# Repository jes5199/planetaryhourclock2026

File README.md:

# Planetary Hour Clock

A clock that shows the planetary hour, the day of the week, and the old unequal
(temporal) hours of day and night, all on one printed dial that stays correct
all year. Everything that changes with the seasons is handled by *speed*, not
drawing: the hands and LEDs speed up and slow down, so sunrise is always at the
same place on the dial.

- Two mechanical hands: a temporal hour hand and a gold planetary-hour hand
- An 84-LED day ring, plus 18 LEDs on the star and compass points
- A round AMOLED in the centre showing civil time, the hour's ruling planet, and how long
  the current hour is

The design, the dial and the maths are written up in the design doc,
[The planetary hours clock: how it works](https://claude.ai/artifact/MR7kYXaauj6WffYWu9YXEm).

## Status

| Part | State |
| --- | --- |
| Centre screen | Working: clock face, setup by phone or touchscreen, settings saved in flash |
| Hands | Servo board running our firmware; both servos turn freely past one revolution. Next: link it to the screen board over ESP-NOW (plan in [`hands/README.md`](hands/README.md#link-to-the-screen-board-planned-esp-now)). |
| Dial PCB | Generated (KiCad 9), DRC clean; LED-window test coupon ready to order |
| LED board | Generated (KiCad 9, DRC clean): 102 LEDs and the 12 V → 5 V power hub, BOM and placement files for JLCPCB assembly; not ordered |
| Power | One 12 V ≥ 3 A brick into the LED board, which feeds the servo board (12 V) and the screen (5 V) |

## Hardware

| Part | What | Notes |
| --- | --- | --- |
| Centre screen and main controller | [Waveshare ESP32-S3-Touch-AMOLED-1.43](https://www.waveshare.com/esp32-s3-touch-amoled-1.43.htm) | 466×466 round AMOLED, touch, PCF85063 RTC |
| Hand drive | [Waveshare Servo Driver with ESP32](https://www.waveshare.com/Servo-Driver-with-ESP32.htm) (ESP32-D0WD-V3, 4 MB flash, CP2102 USB serial) + 2× Feetech STS3215 serial bus servos, 12 V version | On the desk, running `hands/`. The screen board will send the hand angles to it. |
| Servo power | 12 V DC brick, ≥ 2 A, 5.5 × 2.1 mm centre-positive plug | The board passes its input straight to the servos, so it must match their 12 V rating. USB alone runs the ESP32 but not the servos. |
| Main battery (optional) | 3.7 V single-cell LiPo, MX1.25 2-pin plug, ≥ 500 mAh | Charged by the board at 0.5 A. Check polarity before plugging in. |
| RTC backup | Rechargeable 3 V ML1220 on the SH1.0 2-pin "RTC" header | The header trickle-charges, so never use a CR (non-rechargeable) cell. Without one, the time is lost when power is cut and the clock asks to be set up again. |

## Layout

- `firmware/`: the screen board's firmware (PlatformIO). See [`firmware/README.md`](firmware/README.md).
- `hands/`: the servo board's firmware (PlatformIO). See [`hands/README.md`](hands/README.md).
- `hardware/`: the PCBs, generated as KiCad source. See [`hardware/README.md`](hardware/README.md).
- `tools/`: scripts that generate the firmware's time-zone and city tables, and their source data.

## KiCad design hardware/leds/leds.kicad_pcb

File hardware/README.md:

# Hardware

PCBs for the clock, generated as KiCad 9 source by Python scripts. Edit the scripts, not the
`.kicad_pcb` files: re-running a script rewrites its board.

| Board | Script | What |
| --- | --- | --- |
| `dial/dial.kicad_pcb` | `gen_dial.py` | The 146 mm front dial: all the artwork, the LED windows, the centre hole |
| `coupon/coupon.kicad_pcb` | `gen_coupon.py` | A 78 × 34 mm test coupon of eight LED-window styles |
| `leds/leds.kicad_pcb` | `gen_leds.py` | The LED board behind the dial: 102 addressable LEDs, and the clock's power hub |

The dial follows mockup **N · 84-LED day ring** in the "Planetary Hours Dial" design canvas: its
SVG units are converted at 23/102 mm per unit (the 46 mm screen is r = 102 there), which puts
the rim at r = 73 mm, as in the design doc.

## Inks

A PCB has three: **gold** (bare ENIG copper where the solder mask is opened), **black** (the
mask) and **white** (silkscreen). LED windows are a fourth: **bare fibreglass**, with copper
and mask cleared on both faces, lit from an LED board behind.

| Dial element | Ink |
| --- | --- |
| Rim, ring lines, slice edges, ticks, star | Gold |
| Compass rose | Each point split down its spine: anticlockwise facet gold, clockwise facet white; diagonals under cardinals, the rose over everything else |
| Ruler band, daytime half of each slice | Gold, with the day ruler's symbol knocked out in black |
| Ruler band, night quarters | Black, with the night ruler's symbol in white |
| Day names | White, bent along the arc of their band |
| Planet names, hour numerals | White (numerals crossing the rose's white facets are knocked out in black) |
| Daytime half of the hour ring | Copper under the black mask (a faint sheen) |
| 84 rim LEDs, 7 star points, 7 star corners, 4 compass tips | Fibreglass windows, each with a 0.5 mm non-plated pinhole drilled through its centre |

Gold edges are defined by the mask openings; the copper underneath extends 0.1 mm further so
small registration errors don't show bare edges.

## Fab notes

- **Thickness 0.8 mm** (in the board stackup): brighter windows than 1.6 mm.
- **Black solder mask, white silkscreen, ENIG finish**, both sides (also in the stackup).
- The centre hole (6.5 mm) clears the hands' tube stack, all K&S telescoping brass (0.014"
  wall): a fixed 5/32" post that holds the screen and carries its 5 V and GND wires, the gold
  hand's 3/16" tube on it, and the hour hand's 7/32" tube (5.56 mm) outside that. Nothing else
  can hold the screen up: the hands sweep the whole gap between the dial and the screen.
- Four M2.5 standoff holes (2.7 mm, non-plated) at 14 mm radius on the diagonals, inside the
  46 mm screen's shadow so they never show. The hands sweep between the dial and the screen, so
  standoffs go *behind* the dial (to the LED board and frame), not in front. Their screw heads sit on the dial's face, inside the hands' sweep: the lowest hand must
  run at least 2.5 mm above the dial (an M2.5 pan head is ~2 mm tall; the 0.8 mm dial can't be
  countersunk). Decided 2026-11-18.
- Balancing copper on the back: a 45° cross-hatch (0.4 mm lines 2.26 mm apart, ~31% copper against
  the front's ~25%), under the back's black mask and clear of the windows, holes and edge. The
  dial is held only near its centre, so a balanced board bows less at the rim (`BACK_HATCH`).
- 102 pinholes, 0.5 mm non-plated (the usual fab minimum for NPTH; `PINHOLE_D` in `gen_dial.py`).
- Silk glyphs are grown by 0.035 mm so Cormorant Garamond's hairlines survive silkscreen.
- Order the coupon at 0.8 mm and 1.6 mm, light it from behind, and pick a window style (and a
  board thickness) before ordering the dial.

## LED board

Same outline, centre hole and standoff holes as the dial, sitting a few millimetres behind it.
It takes the LED positions from `gen_dial.led_sites()`, so a window and its LED can't drift
apart. Assembled by JLCPCB on **both sides**; 1.6 mm, black mask, ENIG (gold) finish, so it can
carry the servo board.

**Front** (facing the dial): only the 102 LEDs and a 100 nF capacitor each, so it stays flat.
Copper: a 5 V pour plus the data tracks, and a small GND island under the regulator.

**Back**: the power hub and connectors, a GND pour, and four M2.5 holes (58 × 23 mm) for the
servo board, currently in the lower half until the hand mechanism is designed (`SERVO_CENTRE`).
No pour copper within 3 mm of any mounting hole on either face, and no track or via within
3.3 mm of one (the generator bends tracks around them), so a screw head or standoff scratched
through the mask can't short anything. The dial's standoffs are at 14 mm radius, 2.7 mm clear of
the servo board's top edge.

The DC jack, the protection FET, TVS, bulk capacitor, J2 and the regulator sit together at the
bottom right, in the band between the star points and the rim LEDs. J3 is just above the centre hole,
J4 just past the servo board's left end (seen from the front). No pour copper under the servo
board's ESP32 antenna (both faces), since its radio links it to the screen board.

| Connector | Part | Pins | Goes to |
| --- | --- | --- | --- |
| J1 12V IN | SMD 5.5 × 2.1 mm DC jack, XKB DC-005-5A-2.0-SMT (C319134), rated 2.5 A (JLCPCB's data; the "5A" in the name is a series code) | centre +12 V, sleeve GND, switch GND | A regulated 12 V brick (2–3 A is plenty; a bigger one is fine, the jack limits what's drawn). At 6 o'clock, mouth 0.3 mm in from the board edge (so its corners don't overhang): the cord leaves the bottom of the clock |
| J2 12V SERVO | JST XH 2-pin | 1 +12 V, 2 GND | The servo board's barrel jack: a short (10–15 cm, ≥ 22 AWG) lead with a 5.5 × 2.1 mm plug, centre + on pin 1. Use a right-angle plug: a straight one reaches nearly to this board's edge |
| J3 5V SCREEN | JST XH 2-pin, just above the centre hole | 1 +5 V (≈4.7 V, through the SS14), 2 GND | The screen board's 5 V pin (2×14 header J1 pin 4, GND pin 6), wires straight up the centre post |
| J4 LED DATA | HCTL HC-1.25-3PLT (C2845389), 1.25 mm (MX1.25 / PicoBlade-style) 3-pin, surface mount, vertical, on Molex 53398-0371's land pattern (Molex's own part had 6 in stock) | 1 nc, 2 GND, 3 data | The servo board's RGB-LED header H1 (5 V, GND, LED-OUT): a straight 1:1 cable; its 5 V pin lands on nc. Placed 10 mm (courtyard to board edge) past the servo board's left end (seen from the front), where H1's side-entry cable leaves (`J4_CLEAR`), assuming the servo board mounts with its ports, OLED and jacks facing out and its DC jack towards J2. Buzz the cable out: H1's pin-1 end isn't marked. H1 is a 1.25 mm MX1.25/PicoBlade-style header (Waveshare calls it "XH1.25"; checked 2026-11-18: its plug pulls straight out, no latch, so not JST GH), so a double-ended MX1.25 3-pin cable mates with both |

**Power.** 12 V in → Q1, an AO4407A P-channel MOSFET wired as an "ideal diode" for reverse-polarity
protection (drain to the jack, source to the rail, gate to GND through 100k: 13 mΩ, so ~0.05 W at
2 A where a Schottky would drop 0.5 V and make 1 W; reversed, it stays off; its 25 V gate rating
needs no zener) → a 13 V TVS (SMAJ13A) and 100 µF bulk
capacitor, which damp the ring when a live brick is plugged in (the TVS clamps at 21.5 V at its
  full rated pulse, above the regulator's 19 V limit, but hot-plug ringing into 100 µF is far
  smaller than that pulse) → 12 V
to the servo board, and to a TPS563201 buck (3 × 10 µF in, 4.7 µH, 3 × 22 µF out, 56k/10k: 5.07 V,
up to 3 A) → 5 V for the LEDs and, through an SS14, the screen. EN is tied to VIN (both rated
19 V). The regulator's GND pin and input capacitors drop through vias to a GND island on the
front, right under the chip, so the input current loop is a few millimetres. The power path
(jack → Q1 → J2) runs on copper pours. Pad connections to the pours: thermal relief on the
front (the LEDs and their 0402 capacitors, so both ends of each heat evenly during reflow), solid
for every part on the back (the power parts need the copper for current and heat). U1's GND pin
also has two vias straight down to the front island.

Things the hardware doesn't protect against, so the firmware must:
- **Servo stall current.** Two STS3215s stalling draw ~2.7 A each, more than the jack's 2.5 A,
  and through the jack. Set the servos' torque limit so a jammed hand can't
  pull that. Normal running (hands moving slowly, LEDs mostly dim) is well under 1 A.
- **Brightness.** The XL-2020 LEDs draw up to 5 mA per colour, so all 102 at full white is about
  1.5 A, inside the regulator's 3 A. A firmware cap is still sensible (the screen and heat share
  the budget), and the dial only ever lights a few LEDs brightly. Check the colour order (GRB for
  WS2812B) when the firmware first drives them.
- The SS14 on the screen feed exists because the screen board's 5 V header pin **is its USB
  VBUS**: without it, plugging the screen board into a computer while the clock is powered would
  connect this board's 5 V to the computer's USB port, and a computer alone would try to power
  the LEDs.

**Data chain** (written to `leds/led-chain.csv` with each LED's angle): the servo board's two
on-board LEDs come first, then here: rim LEDs 0–83 clockwise from the start of Sunday's slice
(so chain index = the firmware's `dayRingLed`), then the 7 star points, the 7 star corners and the
4 compass tips, each set clockwise. Jumps between sets go through the back. The input runs from
J4 (through 1k, with a 100k pull-down so LED 0's input doesn't float when the servo board is off)
round the back, crosses to the front in the star ring's one gap (between star
points 6 and 0, which the chain jumps through the back), and comes in to LED 0's DIN.

**Parts not in KiCad's library** live in `footprints/jlc.pretty` (`kicadart.Part` looks there
first):
- The LEDs: XINGLIGHT XL-2020RGBC-WS2812B (C5349955), a WS2812B-protocol LED in the 2020 package,
  because Worldsemi's own WS2812B-2020 (C965555) was out of stock. Footprint drawn from its
  datasheet's recommended pattern and numbered like KiCad's WS2812B-2020 (1 DO, 2 GND, 3 DI,
  4 VDD), which is its datasheet top view turned 180°.
- The DC jack: imported from JLCPCB's part data with easyeda2kicad (in the venv:
  `.venv/bin/easyeda2kicad --footprint --3d --lcsc_id C319134 --output footprints/jlc`),
  converted with `kicad-cli fp upgrade`, pads set from XKB's drawing (rev A1, 2025-07-19). Its
  3D model doesn't show in KiCad's render.

**Placement file.** JLCPCB places its *own* library footprint for each part, and those often
differ from KiCad's: the LEDs and the regulator have pin 1 in the opposite corner (180°), and
connectors are centred where KiCad puts pin 1 at the origin. `jlc_ref.py` downloads JLCPCB's
footprint for every LCSC part (easyeda2kicad, cached in `out/jlc-ref/`), matches its pads to ours,
and records the turn and offset; `cpl.py` (KiCad's Python) writes the CPL from the board with those
corrections. Most need 0° or 180°; the SO-8 FET needs 90°. `jlc_ref.py` has an override table
for parts whose JLCPCB pad numbers don't follow their polarity marks (an earlier SS54 numbered
its cathode end "2"; matching by number would have put it in backwards). A check that places JLCPCB's footprints by the
finished CPL lands every pad on ours (within 0.03 mm for the LEDs, 0.2 mm for the regulator and
diodes, where the two libraries' pads differ in size).

**Reviewed** (2026-11-18) eight times by independent agents against the datasheets: pinouts,
the LED chain, the buck design, JLCPCB rules and stock, the CPL against JLCPCB's footprints, and
the fit with the dial. Their findings are fixed above.

Before ordering:
- Upload `out/leds-jlc/` to JLCPCB's quote page and check every part in the assembly preview.
  The CPL is corrected to JLCPCB's footprints, but the back side relies on the mirrored
  convention (180° − angle) that kicad-jlcpcb-tools and KiBot use; JLCPCB doesn't document it and
  has changed it before. Odd back-side angles (U1 at 330°, Q1 at 258°) make a wrong
  convention obvious in the preview. Check especially: the LEDs (data out at the package's marked
  corner, which is the silk tick), U1's pin-1 dot, Q1's pin-1 dot (at its J2-side, inward corner; pin 4, the gate, is beside its 100k), the SMAJ13A's cathode band towards
  the +12 V side, C111's + at the J2 side, and J2/J3's latches.
- Tell JLCPCB the LEDs are MSL 5 (bake before use) and ask for a reflow peak of 245 °C or less:
  the datasheet recommends 240 ± 5 °C for 6 s (260 °C is the absolute maximum), at most two
  reflows, the second within 8 hours of the first and let them choose the reflow order: the back carries the heavy parts (the 11 mm jack, C111, L1), which shouldn't
  hang upside down through a second pass.
- Check stock (2026-11-18): LEDs C5349955 ~80k (listed by LCSC as "XL-2020RGBC-2812B"; its
  datasheet says XL-2020RGBC-WS2812B), jack C319134 ~4.4k, inductor C408410 ~7k at JLCPCB (LCSC's
  product page is broken; fallback Sunlord SWPA5040S4R7MT, C48496), 1.25 mm header C2845389 ~49k,
  AO4407A C16072 ~9k, JST XH C158012 ~474k, TPS563201 ~4.3k. All extended parts.
- A round board with parts near the edge may need JLCPCB's break-off rails for assembly. The rim
  LEDs' pads are 0.93 mm from the edge all the way round, so ask for tabs placed between parts,
  and none at 6 o'clock, where the DC jack's mouth is 0.3 mm in from the edge.
- The through-hole connector pins poke ~1.5 mm out of the front: the gap to the dial (and any
  baffle) has to clear them. J3 sits on the back just above the centre hole, where the hand tubes'
  gears will be: move it (`J3_R`) if the gear train needs that space.
- Measure the servo board's hole spacing with calipers (58 × 23 mm, from Waveshare's dimension
  drawing).
- KiCad's DRC reports 0 errors and 0 unconnected; the only warnings are `lib_footprint_mismatch`,
  because the generator strips the hidden silkscreen from the library footprints.

## Build

```sh
cd hardware
python3 -m venv .venv && .venv/bin/pip install -r requirements.txt
.venv/bin/python gen_dial.py      # -> dial/dial.kicad_pcb
.venv/bin/python gen_coupon.py    # -> coupon/coupon.kicad_pcb
./render.sh dial/dial.kicad_pcb   # DRC + SVG + 3D render into out/ (uses KiCad 9's kicad-cli)

.venv/bin/python gen_leds.py      # -> leds/leds.kicad_pcb, leds-bom.csv, led-chain.csv
./fill_zones.sh leds/leds.kicad_pcb   # fill the copper pours (KiCad's own filler, via its Python)
./render.sh leds/leds.kicad_pcb
./jlc.sh leds/leds.kicad_pcb      # -> out/leds-jlc/: gerbers.zip, bom.csv, cpl.csv for JLCPCB
                                  #    (CPL corrected to JLCPCB's footprints: jlc_ref.py + cpl.py)
```

Boards with parts (`gen_leds.py`) place KiCad's own library footprints (read from the KiCad app),
set their nets, and write tracks, vias and zone outlines; `kicadart.Part` computes pad positions
the way KiCad does, including mirroring for the back. KiCad fills the zones, since its clearance
and island rules decide connectivity; DRC then confirms every pad is connected.

`template.kicad_pcb` is an empty KiCad 9 board with the stackup; scripts append their
`gr_poly`, `gr_circle` and footprint s-expressions to it (`kicadart.py`).

## Fonts

`fonts/` holds Cormorant Garamond (names and numerals) and Noto Sans Symbols (planet
symbols), both under the SIL Open Font License (texts alongside). Noto Sans Symbols has no ☉,
so the Sun is drawn as a ring and dot.

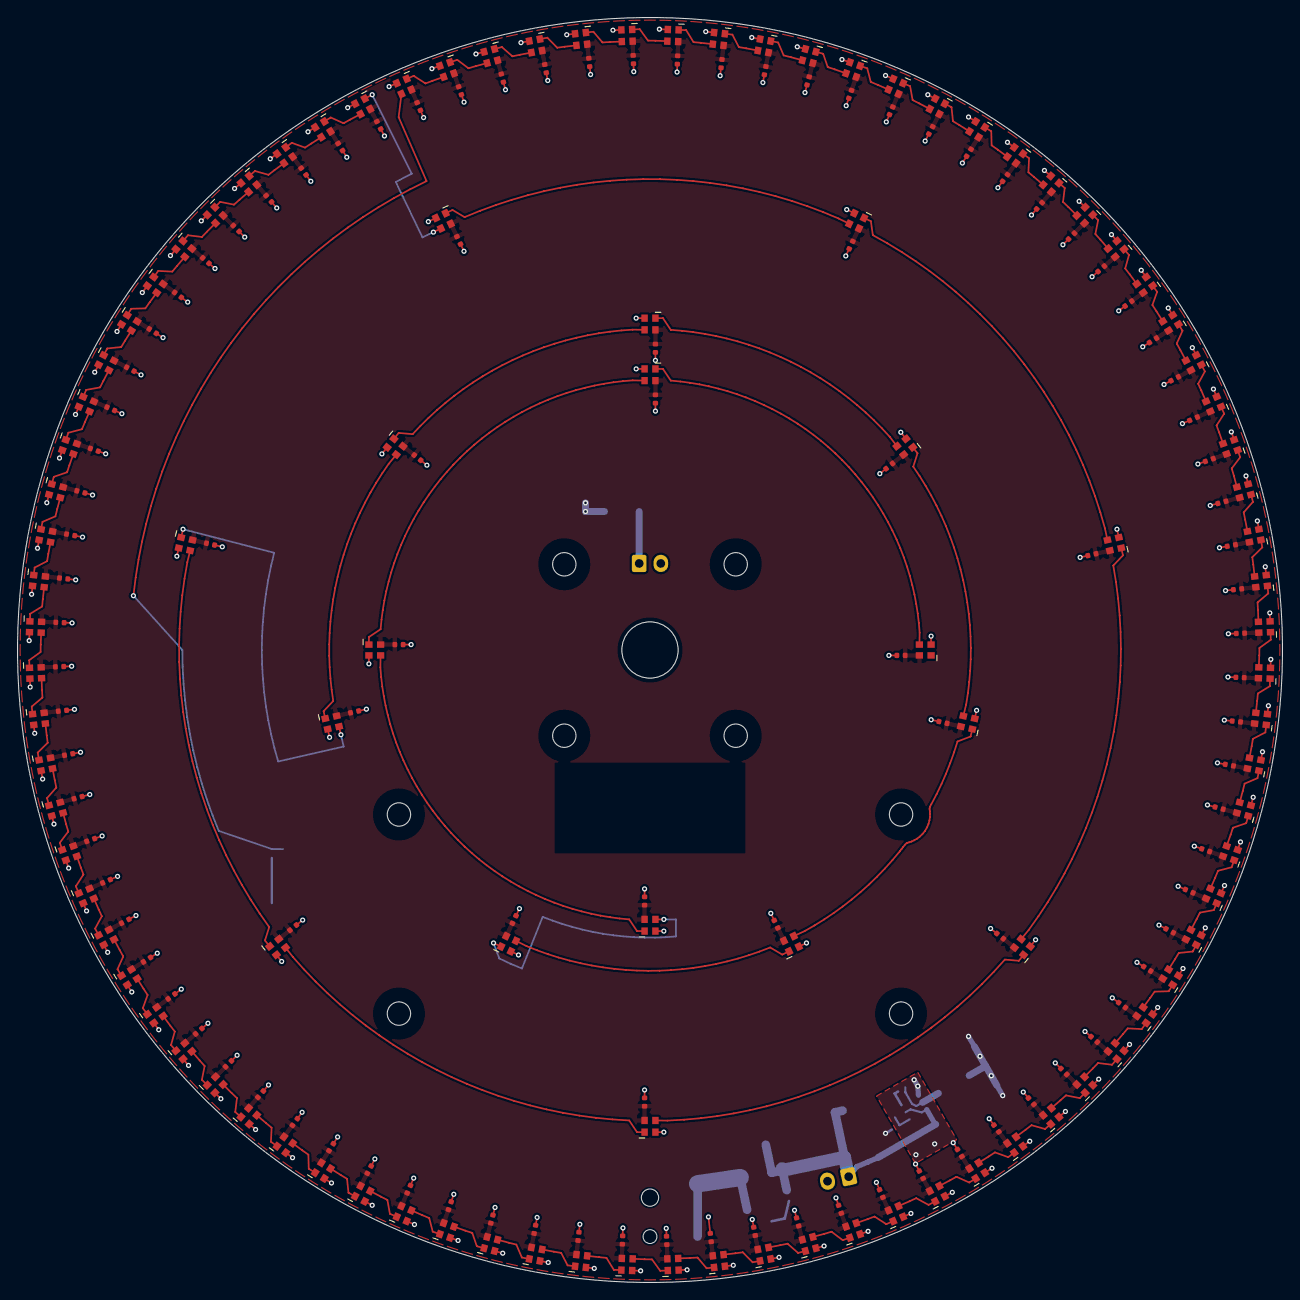
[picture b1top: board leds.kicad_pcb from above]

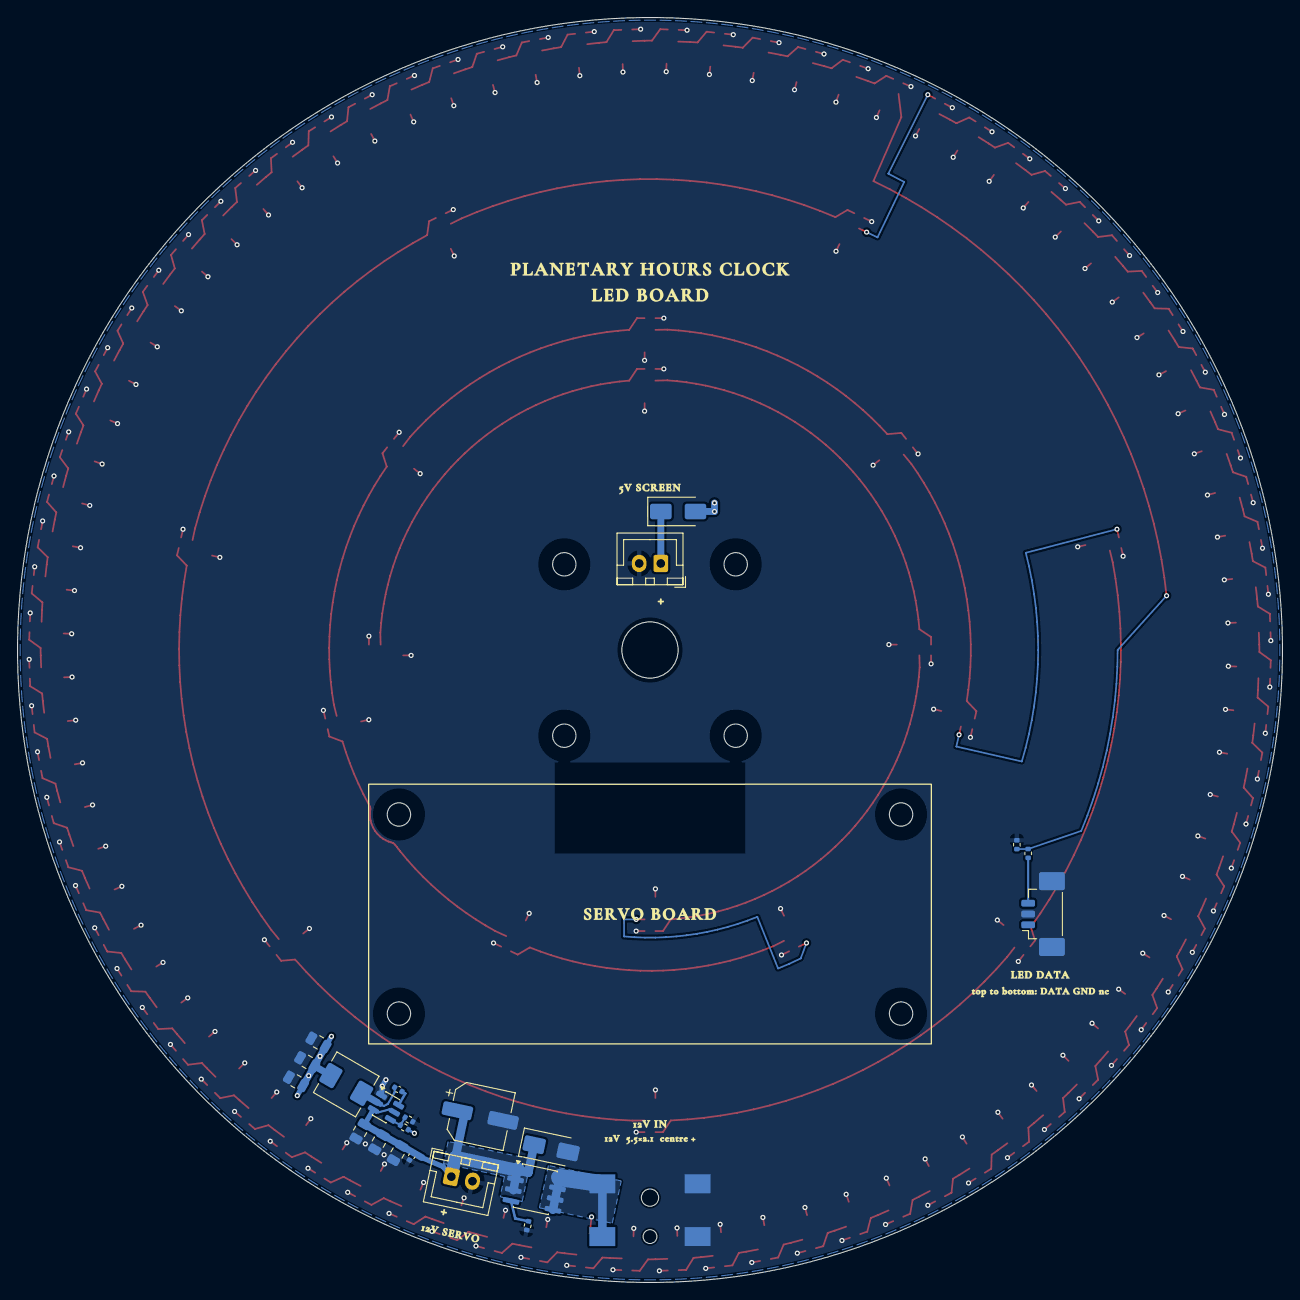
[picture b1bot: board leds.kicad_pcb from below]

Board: 2 copper layers, 146.1 x 146.1 mm, 235 parts (23 on the bottom side), 112 nets.

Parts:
C1, C2, C3, C4, C5, C6, C7, C8, C9, C10, C11, C12, C13, C14, C15, C16, C17, C18, C19, C20, C21, C22, C23, C24, C25, C26, C27, C28, C29, C30, C31, C32, C33, C34, C35, C36, C37, C38, C39, C40, C41, C42, C43, C44, C45, C46, C47, C48, C49, C50, C51, C52, C53, C54, C55, C56, C57, C58, C59, C60, C61, C62, C63, C64, C65, C66, C67, C68, C69, C70, C71, C72, C73, C74, C75, C76, C77, C78, C79, C80, C81, C82, C83, C84, C85, C86, C87, C88, C89, C90, C91, C92, C93, C94, C95, C96, C97, C98, C99, C100, C101, C102, C107: 100nF; C_0402_1005Metric
C103, C104, C105: 10uF 25V; C_0805_2012Metric
C106: 100nF 50V; C_0402_1005Metric
C108, C109, C110: 22uF 25V; C_0805_2012Metric
C111: 100uF 35V; CP_Elec_6.3x7.7
D1, D2, D3, D4, D5, D6, D7, D8, D9, D10, D11, D12, D13, D14, D15, D16, D17, D18, D19, D20, D21, D22, D23, D24, D25, D26, D27, D28, D29, D30, D31, D32, D33, D34, D35, D36, D37, D38, D39, D40, D41, D42, D43, D44, D45, D46, D47, D48, D49, D50, D51, D52, D53, D54, D55, D56, D57, D58, D59, D60, D61, D62, D63, D64, D65, D66, D67, D68, D69, D70, D71, D72, D73, D74, D75, D76, D77, D78, D79, D80, D81, D82, D83, D84, D85, D86, D87, D88, D89, D90, D91, D92, D93, D94, D95, D96, D97, D98, D99, D100, D101, D102: XL-2020RGBC-WS2812B; LED_XL-2020RGBC-WS2812B_C5349955
D103: SMAJ13A; D_SMA
D104: SS14; D_SMA
H1, H2, H3, H4, H5, H6, H7, H8: hole; Hole_2.7mm
J1: DC-005-5A-2.0-SMT; DC-005-5A-2.0-SMT_C319134
J2, J3: B2B-XH-A; JST_XH_B2B-XH-A_1x02_P2.50mm_Vertical
J4: HC-1.25-3PLT; HC-1.25-3PLT_C2845389
L1: 4.7uH MWSA0503S; L_Sunlord_MWSA0503S
Q1: AO4407A; SOIC-8_3.9x4.9mm_P1.27mm
R1: 56k; R_0402_1005Metric
R2: 10k; R_0402_1005Metric
R3, R5: 100k; R_0402_1005Metric
R4: 1k; R_0402_1005Metric
U1: TPS563201DDCR; TSOT-23-6

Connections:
+5V: C1.1, C2.1, C3.1, C4.1, C5.1, C6.1, C7.1, C8.1, C9.1, C10.1, C11.1, C12.1, C13.1, C14.1, C15.1, C16.1, C17.1, C18.1, C19.1, C20.1, C21.1, C22.1, C23.1, C24.1, C25.1, C26.1, C27.1, C28.1, C29.1, C30.1, C31.1, C32.1, C33.1, C34.1, C35.1, C36.1, C37.1, C38.1, C39.1, C40.1, C41.1, C42.1, C43.1, C44.1, C45.1, C46.1, C47.1, C48.1, C49.1, C50.1, C51.1, C52.1, C53.1, C54.1, C55.1, C56.1, C57.1, C58.1, C59.1, C60.1, C61.1, C62.1, C63.1, C64.1, C65.1, C66.1, C67.1, C68.1, C69.1, C70.1, C71.1, C72.1, C73.1, C74.1, C75.1, C76.1, C77.1, C78.1, C79.1, C80.1, C81.1, C82.1, C83.1, C84.1, C85.1, C86.1, C87.1, C88.1, C89.1, C90.1, C91.1, C92.1, C93.1, C94.1, C95.1, C96.1, C97.1, C98.1, C99.1, C100.1, C101.1, C102.1, C108.1, C109.1, C110.1, D1.4, D2.4, D3.4, D4.4, D5.4, D6.4, D7.4, D8.4, D9.4, D10.4, D11.4, D12.4, D13.4, D14.4, D15.4, D16.4, D17.4, D18.4, D19.4, D20.4, D21.4, D22.4, D23.4, D24.4, D25.4, D26.4, D27.4, D28.4, D29.4, D30.4, D31.4, D32.4, D33.4, D34.4, D35.4, D36.4, D37.4, D38.4, D39.4, D40.4, D41.4, D42.4, D43.4, D44.4, D45.4, D46.4, D47.4, D48.4, D49.4, D50.4, D51.4, D52.4, D53.4, D54.4, D55.4, D56.4, D57.4, D58.4, D59.4, D60.4, D61.4, D62.4, D63.4, D64.4, D65.4, D66.4, D67.4, D68.4, D69.4, D70.4, D71.4, D72.4, D73.4, D74.4, D75.4, D76.4, D77.4, D78.4, D79.4, D80.4, D81.4, D82.4, D83.4, D84.4, D85.4, D86.4, D87.4, D88.4, D89.4, D90.4, D91.4, D92.4, D93.4, D94.4, D95.4, D96.4, D97.4, D98.4, D99.4, D100.4, D101.4, D102.4, D104.2, L1.2, R1.2
+5V_SCREEN: D104.1, J3.1
+12V: C103.1, C104.1, C105.1, C106.1, C111.1, D103.1, J2.1, Q1.1, Q1.2, Q1.3, U1.3, U1.5
+12V_IN: J1.1, Q1.5, Q1.6, Q1.7, Q1.8
FB: R1.1, R2.1, U1.4
GATE: Q1.4, R3.1
GND: C1.2, C2.2, C3.2, C4.2, C5.2, C6.2, C7.2, C8.2, C9.2, C10.2, C11.2, C12.2, C13.2, C14.2, C15.2, C16.2, C17.2, C18.2, C19.2, C20.2, C21.2, C22.2, C23.2, C24.2, C25.2, C26.2, C27.2, C28.2, C29.2, C30.2, C31.2, C32.2, C33.2, C34.2, C35.2, C36.2, C37.2, C38.2, C39.2, C40.2, C41.2, C42.2, C43.2, C44.2, C45.2, C46.2, C47.2, C48.2, C49.2, C50.2, C51.2, C52.2, C53.2, C54.2, C55.2, C56.2, C57.2, C58.2, C59.2, C60.2, C61.2, C62.2, C63.2, C64.2, C65.2, C66.2, C67.2, C68.2, C69.2, C70.2, C71.2, C72.2, C73.2, C74.2, C75.2, C76.2, C77.2, C78.2, C79.2, C80.2, C81.2, C82.2, C83.2, C84.2, C85.2, C86.2, C87.2, C88.2, C89.2, C90.2, C91.2, C92.2, C93.2, C94.2, C95.2, C96.2, C97.2, C98.2, C99.2, C100.2, C101.2, C102.2, C103.2, C104.2, C105.2, C106.2, C108.2, C109.2, C110.2, C111.2, D1.2, D2.2, D3.2, D4.2, D5.2, D6.2, D7.2, D8.2, D9.2, D10.2, D11.2, D12.2, D13.2, D14.2, D15.2, D16.2, D17.2, D18.2, D19.2, D20.2, D21.2, D22.2, D23.2, D24.2, D25.2, D26.2, D27.2, D28.2, D29.2, D30.2, D31.2, D32.2, D33.2, D34.2, D35.2, D36.2, D37.2, D38.2, D39.2, D40.2, D41.2, D42.2, D43.2, D44.2, D45.2, D46.2, D47.2, D48.2, D49.2, D50.2, D51.2, D52.2, D53.2, D54.2, D55.2, D56.2, D57.2, D58.2, D59.2, D60.2, D61.2, D62.2, D63.2, D64.2, D65.2, D66.2, D67.2, D68.2, D69.2, D70.2, D71.2, D72.2, D73.2, D74.2, D75.2, D76.2, D77.2, D78.2, D79.2, D80.2, D81.2, D82.2, D83.2, D84.2, D85.2, D86.2, D87.2, D88.2, D89.2, D90.2, D91.2, D92.2, D93.2, D94.2, D95.2, D96.2, D97.2, D98.2, D99.2, D100.2, D101.2, D102.2, D103.2, J1.2, J1.3, J2.2, J3.2, J4.2, J4.MP, R2.2, R3.2, R5.2, U1.1
LED_D1: D1.1, D2.3
LED_D2: D2.1, D3.3
LED_D3: D3.1, D4.3
LED_D4: D4.1, D5.3
LED_D5: D5.1, D6.3
LED_D6: D6.1, D7.3
LED_D7: D7.1, D8.3
LED_D8: D8.1, D9.3
LED_D9: D9.1, D10.3
LED_D10: D10.1, D11.3
LED_D11: D11.1, D12.3
LED_D12: D12.1, D13.3
LED_D13: D13.1, D14.3
LED_D14: D14.1, D15.3
LED_D15: D15.1, D16.3
LED_D16: D16.1, D17.3
LED_D17: D17.1, D18.3
LED_D18: D18.1, D19.3
LED_D19: D19.1, D20.3
LED_D20: D20.1, D21.3
LED_D21: D21.1, D22.3
LED_D22: D22.1, D23.3
LED_D23: D23.1, D24.3
LED_D24: D24.1, D25.3
LED_D25: D25.1, D26.3
LED_D26: D26.1, D27.3
LED_D27: D27.1, D28.3
LED_D28: D28.1, D29.3
LED_D29: D29.1, D30.3
LED_D30: D30.1, D31.3
LED_D31: D31.1, D32.3
LED_D32: D32.1, D33.3
LED_D33: D33.1, D34.3
LED_D34: D34.1, D35.3
LED_D35: D35.1, D36.3
LED_D36: D36.1, D37.3
LED_D37: D37.1, D38.3
LED_D38: D38.1, D39.3
LED_D39: D39.1, D40.3
LED_D40: D40.1, D41.3
LED_D41: D41.1, D42.3
LED_D42: D42.1, D43.3
LED_D43: D43.1, D44.3
LED_D44: D44.1, D45.3
LED_D45: D45.1, D46.3
LED_D46: D46.1, D47.3
LED_D47: D47.1, D48.3
LED_D48: D48.1, D49.3
LED_D49: D49.1, D50.3
LED_D50: D50.1, D51.3
LED_D51: D51.1, D52.3
LED_D52: D52.1, D53.3
LED_D53: D53.1, D54.3
LED_D54: D54.1, D55.3
LED_D55: D55.1, D56.3
LED_D56: D56.1, D57.3
LED_D57: D57.1, D58.3
LED_D58: D58.1, D59.3
LED_D59: D59.1, D60.3
LED_D60: D60.1, D61.3
LED_D61: D61.1, D62.3
LED_D62: D62.1, D63.3
LED_D63: D63.1, D64.3
LED_D64: D64.1, D65.3
LED_D65: D65.1, D66.3
LED_D66: D66.1, D67.3
LED_D67: D67.1, D68.3
LED_D68: D68.1, D69.3
LED_D69: D69.1, D70.3
LED_D70: D70.1, D71.3
LED_D71: D71.1, D72.3
LED_D72: D72.1, D73.3
LED_D73: D73.1, D74.3
LED_D74: D74.1, D75.3
LED_D75: D75.1, D76.3
LED_D76: D76.1, D77.3
LED_D77: D77.1, D78.3
LED_D78: D78.1, D79.3
LED_D79: D79.1, D80.3
LED_D80: D80.1, D81.3
LED_D81: D81.1, D82.3
LED_D82: D82.1, D83.3
LED_D83: D83.1, D84.3
LED_D84: D84.1, D85.3
LED_D85: D85.1, D86.3
LED_D86: D86.1, D87.3
LED_D87: D87.1, D88.3
LED_D88: D88.1, D89.3
LED_D89: D89.1, D90.3
LED_D90: D90.1, D91.3
LED_D91: D91.1, D92.3
LED_D92: D92.1, D93.3
LED_D93: D93.1, D94.3
LED_D94: D94.1, D95.3
LED_D95: D95.1, D96.3
LED_D96: D96.1, D97.3
LED_D97: D97.1, D98.3
LED_D98: D98.1, D99.3
LED_D99: D99.1, D100.3
LED_D100: D100.1, D101.3
LED_D101: D101.1, D102.3
LED_DATA0: D1.3, R4.2, R5.1
LED_DATA_RAW: J4.3, R4.1
SW: C107.1, L1.1, U1.2
VBST: C107.2, U1.6

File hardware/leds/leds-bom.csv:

Comment,Designator,Footprint,LCSC Part #
100nF,"C1,C2,C3,C4,C5,C6,C7,C8,C9,C10,C11,C12,C13,C14,C15,C16,C17,C18,C19,C20,C21,C22,C23,C24,C25,C26,C27,C28,C29,C30,C31,C32,C33,C34,C35,C36,C37,C38,C39,C40,C41,C42,C43,C44,C45,C46,C47,C48,C49,C50,C51,C52,C53,C54,C55,C56,C57,C58,C59,C60,C61,C62,C63,C64,C65,C66,C67,C68,C69,C70,C71,C72,C73,C74,C75,C76,C77,C78,C79,C80,C81,C82,C83,C84,C85,C86,C87,C88,C89,C90,C91,C92,C93,C94,C95,C96,C97,C98,C99,C100,C101,C102,C107",Capacitor_SMD:C_0402_1005Metric,C1525
10uF 25V,"C103,C104,C105",Capacitor_SMD:C_0805_2012Metric,C15850
100nF 50V,C106,Capacitor_SMD:C_0402_1005Metric,C307331
22uF 25V,"C108,C109,C110",Capacitor_SMD:C_0805_2012Metric,C45783
100uF 35V,C111,Capacitor_SMD:CP_Elec_6.3x7.7,C2836437
XL-2020RGBC-WS2812B,"D1,D2,D3,D4,D5,D6,D7,D8,D9,D10,D11,D12,D13,D14,D15,D16,D17,D18,D19,D20,D21,D22,D23,D24,D25,D26,D27,D28,D29,D30,D31,D32,D33,D34,D35,D36,D37,D38,D39,D40,D41,D42,D43,D44,D45,D46,D47,D48,D49,D50,D51,D52,D53,D54,D55,D56,D57,D58,D59,D60,D61,D62,D63,D64,D65,D66,D67,D68,D69,D70,D71,D72,D73,D74,D75,D76,D77,D78,D79,D80,D81,D82,D83,D84,D85,D86,D87,D88,D89,D90,D91,D92,D93,D94,D95,D96,D97,D98,D99,D100,D101,D102",jlc:LED_XL-2020RGBC-WS2812B_C5349955,C5349955
SMAJ13A,D103,Diode_SMD:D_SMA,C148214
SS14,D104,Diode_SMD:D_SMA,C2480
DC-005-5A-2.0-SMT,J1,jlc:DC-005-5A-2.0-SMT_C319134,C319134
B2B-XH-A,"J2,J3",Connector_JST:JST_XH_B2B-XH-A_1x02_P2.50mm_Vertical,C158012
HC-1.25-3PLT,J4,jlc:HC-1.25-3PLT_C2845389,C2845389
4.7uH MWSA0503S,L1,Inductor_SMD:L_Sunlord_MWSA0503S,C408410
AO4407A,Q1,Package_SO:SOIC-8_3.9x4.9mm_P1.27mm,C16072
56k,R1,Resistor_SMD:R_0402_1005Metric,C25796
10k,R2,Resistor_SMD:R_0402_1005Metric,C25744
100k,"R3,R5",Resistor_SMD:R_0402_1005Metric,C25741
1k,R4,Resistor_SMD:R_0402_1005Metric,C11702
TPS563201DDCR,U1,Package_TO_SOT_SMD:TSOT-23-6,C116592
